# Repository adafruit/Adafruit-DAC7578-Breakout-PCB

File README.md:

## Adafruit DAC7578 - 8 x Channel 12-bit I2C DAC - STEMMA QT / Qwiic PCB

<a href="http://www.adafruit.com/products/6223"><br/>
Click here to purchase one from the Adafruit shop</a>

PCB files for the Adafruit DAC7578 - 8 x Channel 12-bit I2C DAC - STEMMA QT / Qwiic. 

Format is EagleCAD schematic and board layout
* https://www.adafruit.com/product/6223

### Description

If you've ever said to yourself, "Gee, I wish I had eight 12-bit DACs that came in a single package", well I have good news. The Adafruit DAC7578 Breakout is the answer to your wishes! Within its little package, the DAC7578 has eight 12-bit DACs for whatever voltage setting needs you may have, easily controlled over I2C.

The DAC7578 can easily work with 3.3V or 5V power and logic so no matter what microcontroller / microcomputer you're using, you'll get full range output. Note that this DAC is 'ratiometric' - that means that 0 is ground and 4095 is whatever the Vref voltage is. By default the Vref is tied to the power pin, but you could cut a jumper to set the top voltage to anything between 0 and the power pin. E.g. if you want a precision 4.095V reference, you'll need to power with 5V, and provide 4.095V on the VRef pin.

The breakout for the DAC7578 is populated with the required support circuitry to use it with your microcontroller of choice or Blinka-supported computer. The SparkFun Qwiic compatible STEMMA QT JST SH connectors ease the process of connecting the DAC7578 to your project and allows you to easily share an I2C bus with other STEMMA QT, Qwiic, Grove, or other compatible sensors. QT Cable is not included, but we have a variety in the shop. 

Our drivers, wiring diagrams, and example code for Arduino, CircuitPython and Python make it easy to get started so you can get rolling with your project instead of figuring out how to wire things or get the code working.

### License

Adafruit invests time and resources providing this open source design, please support Adafruit and open-source hardware by purchasing products from [Adafruit](https://www.adafruit.com)!

Designed by Limor Fried/Ladyada for Adafruit Industries.

Creative Commons Attribution/Share-Alike, all text above must be included in any redistribution. 
See license.txt for additional details.

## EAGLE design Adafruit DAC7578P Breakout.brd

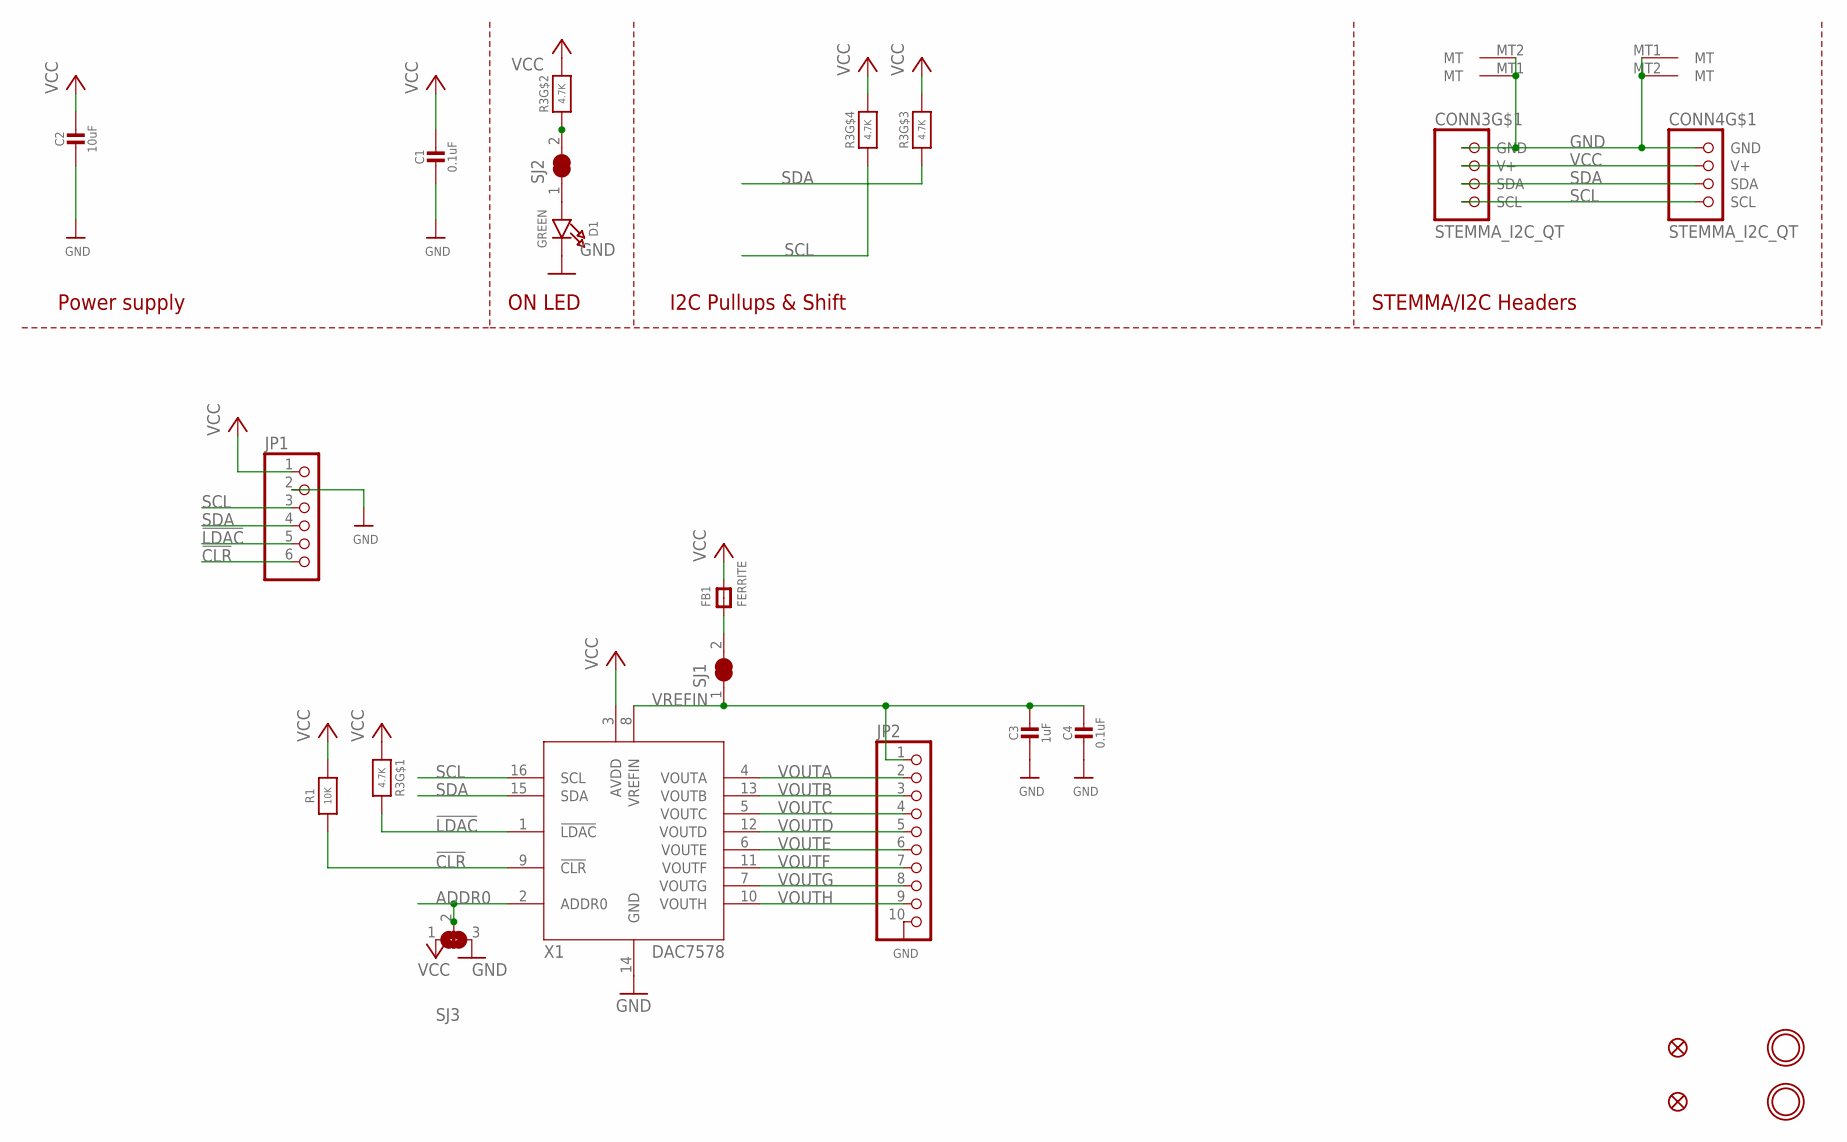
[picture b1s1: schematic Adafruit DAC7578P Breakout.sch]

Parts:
C1, C4: 0.1uF; 0603-NO
C2: 10uF; 0805-NO
C3: 1uF; 0603-NO
CONN3, CONN4: STEMMA_I2C_QT; JST_SH4
D1: GREEN; CHIPLED_0603_NOOUTLINE
FB1: FERRITE; 0603-NO
FID3, FID4: FIDUCIAL_0.5MM
JP1: HEADER-1X670MIL; 1X06_ROUND_70
JP2: HEADER-1X1070MIL; 1X10_ROUND70
R1: 10K; 0603-NO
R3: 4.7K; RESPACK_4X0603
SJ1, SJ2: SOLDERJUMPER_CLOSED; SOLDERJUMPER_CLOSEDWIRE
SJ3: SOLDERJUMPER_2WAY; SOLDERJUMPER_2WAY_OPEN_NOPASTE
U$19, U$21: MOUNTINGHOLE2.5; MOUNTINGHOLE_2.5_PLATED
X1: DAC7578PW; TSSOP16

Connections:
!CLR: JP1.6, R1.1, X1.9 (!CLR)
!LDAC: JP1.5, R3.8 (2), X1.1 (!LDAC)
ADDR0: SJ3.2, X1.2 (ADDR0)
GND: C1.2, C2.2, C3.2, C4.2, CONN3.1 (GND), CONN3.MT1 (MT), CONN3.MT2 (MT), CONN4.1 (GND), CONN4.MT1 (MT), CONN4.MT2 (MT), D1.C, JP1.2, JP2.10, SJ3.3, X1.14 (GND)
unnamed: R3.2 (1), SJ2.2
unnamed: FB1.1, SJ1.2
unnamed: D1.A, SJ2.1
SCL: CONN3.4 (SCL), CONN4.4 (SCL), JP1.3, R3.4 (1), X1.16 (SCL)
SDA: CONN3.3 (SDA), CONN4.3 (SDA), JP1.4, R3.3 (1), X1.15 (SDA)
VCC: C1.1, C2.1, CONN3.2 (V+), CONN4.2 (V+), FB1.2, JP1.1, R1.2, R3.1, R3.5 (2), R3.6 (2), R3.7 (2), SJ3.1, X1.3 (AVDD)
VOUTA: JP2.2, X1.4 (VOUTA)
VOUTB: JP2.3, X1.13 (VOUTB)
VOUTC: JP2.4, X1.5 (VOUTC)
VOUTD: JP2.5, X1.12 (VOUTD)
VOUTE: JP2.6, X1.6 (VOUTE)
VOUTF: JP2.7, X1.11 (VOUTF)
VOUTG: JP2.8, X1.7 (VOUTG)
VOUTH: JP2.9, X1.10 (VOUTH)
VREFIN: C3.1, C4.1, JP2.1, SJ1.1, X1.8 (VREFIN)

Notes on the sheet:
I2C Pullups & Shift
STEMMA/I2C Headers
ON LED
Power supply

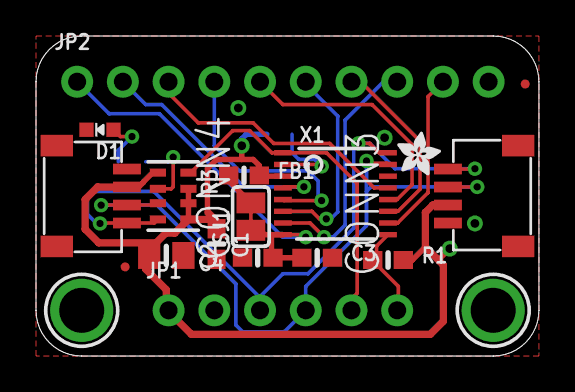
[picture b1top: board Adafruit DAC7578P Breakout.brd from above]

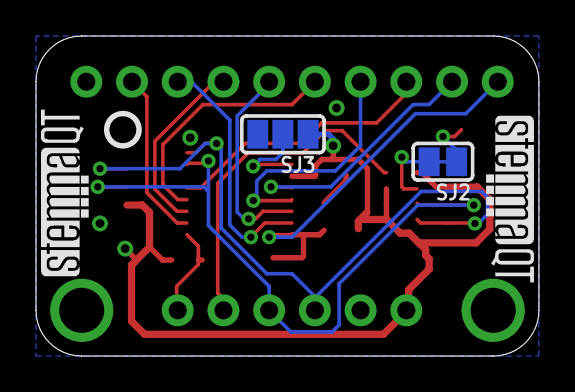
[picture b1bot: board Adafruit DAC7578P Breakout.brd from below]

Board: 2 copper layers, 27.9 x 17.8 mm, 50 parts (11 on the bottom side), 19 nets.

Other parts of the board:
PLABEL0: PLABEL0
PLABEL1: PLABEL1
PLABEL2: PLABEL2
PLABEL3: PLABEL3
PLABEL4: PLABEL4
PLABEL5: PLABEL5
PLABEL6: PLABEL6
PLABEL7: PLABEL7
PLABEL8: PLABEL8
PLABEL9: PLABEL9
PLABEL10: PLABEL10
PLABEL11: PLABEL11
PLABEL12: PLABEL12
PLABEL13: PLABEL13
PLABEL14: PLABEL14
PLABEL15: PLABEL15
PLABEL16: PLABEL16
PLABEL17: PLABEL17
PLABEL18: PLABEL18
PLABEL19: PLABEL19
PLABEL20: PLABEL20
PLABEL21: PLABEL21
PLABEL22: PLABEL22
PLABEL23: PLABEL23
PLABEL24: PLABEL24
PLABEL25: PLABEL25
U$4: ADAFRUIT_2.5MM
U$25: PCBFEAT-REV-040
U$30, U$31: STEMMAQT

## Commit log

2025-02-14 cookiecutter

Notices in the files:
parts and their libraries:
microbuilder: This work is placed in the public domain, and may be freely used for commercial and non-commercial work with the following conditions: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
